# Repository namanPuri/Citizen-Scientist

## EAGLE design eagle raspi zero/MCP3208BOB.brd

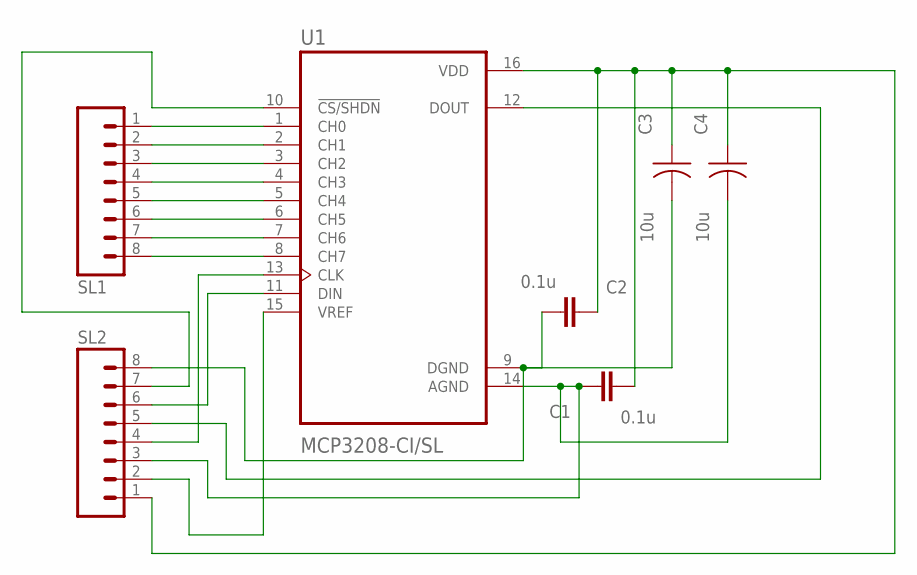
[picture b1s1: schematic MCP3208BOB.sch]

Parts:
C1, C2: 0.1u; CAP_0805
C3, C4: 10u; CAP_TANT_B
SL1, SL2: M08; 08P
U1: MCP3208-CI/SL; SOIC127P600X175-16N

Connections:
unnamed: C1.2, C2.1, C3.1, C4.1, SL2.1, U1.16 (VDD)
unnamed: SL2.6, U1.11 (DIN)
unnamed: C1.1, C4.2, SL2.3, U1.14 (AGND)
unnamed: SL1.1, U1.1 (CH0)
unnamed: SL1.2, U1.2 (CH1)
unnamed: SL1.3, U1.3 (CH2)
unnamed: SL1.4, U1.4 (CH3)
unnamed: SL1.5, U1.5 (CH4)
unnamed: SL1.7, U1.7 (CH6)
unnamed: SL1.6, U1.6 (CH5)
unnamed: SL1.8, U1.8 (CH7)
unnamed: C2.2, C3.2, SL2.8, U1.9 (DGND)
unnamed: SL2.5, U1.12 (DOUT)
unnamed: SL2.7, U1.10 (!CS/SHDN)
unnamed: SL2.4, U1.13 (CLK)
unnamed: SL2.2, U1.15 (VREF)

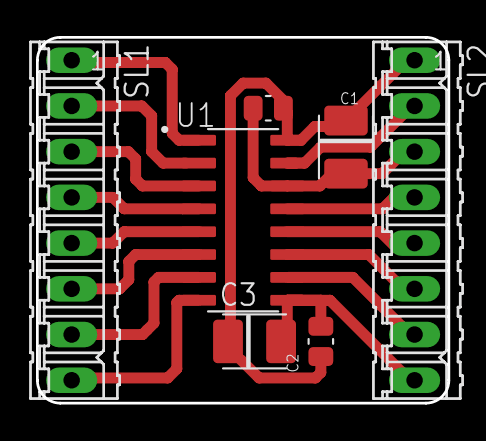
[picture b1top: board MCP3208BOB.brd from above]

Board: 2 copper layers, 22.9 x 20.3 mm, 7 parts (0 on the bottom side), 16 nets.

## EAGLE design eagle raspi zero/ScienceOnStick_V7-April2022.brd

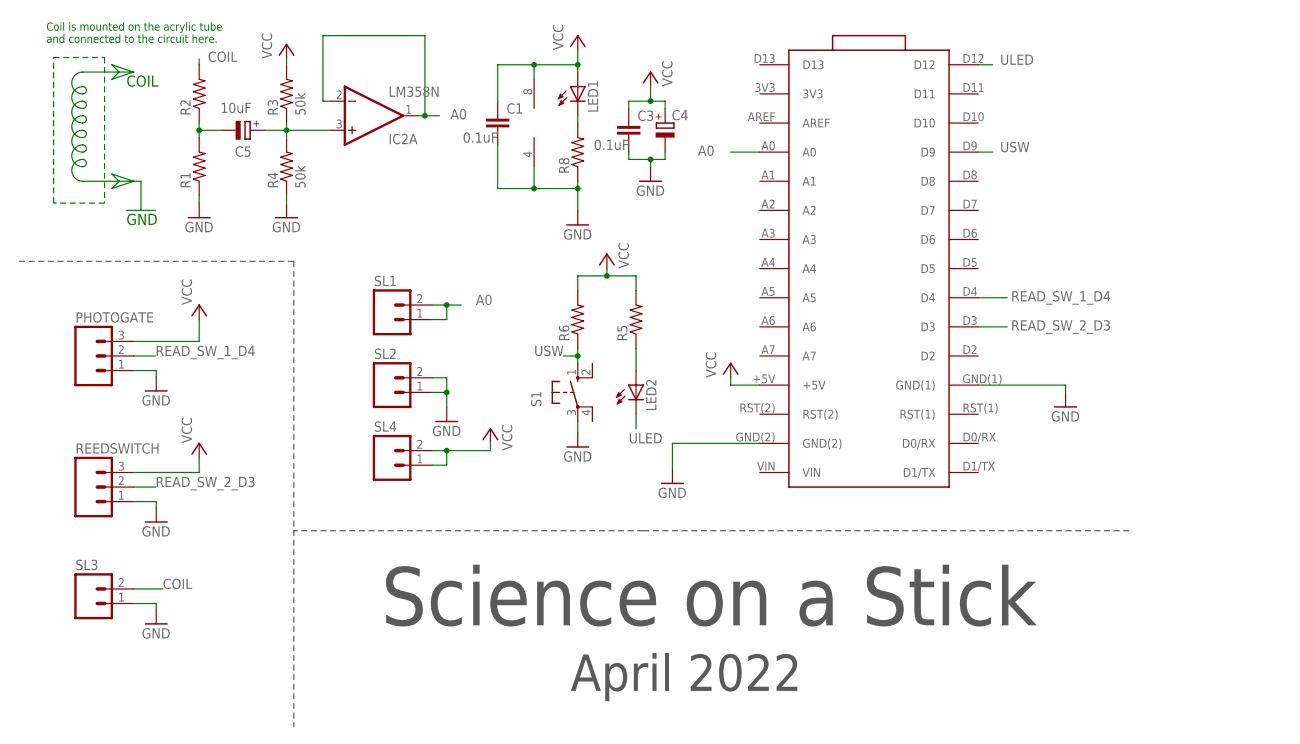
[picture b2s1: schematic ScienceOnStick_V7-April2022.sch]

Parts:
C1, C3: 0.1uF; C025-025X050
C4: CPOL-EUE2.5-6; E2,5-6
C5: 10uF; E2,5-6
IC2: LM358N; DIL08
LED1, LED2: LED3MM
PHOTOGATE: M03; 03P
R1, R2, R5, R6, R8: RESISTOR0207/7; 0207/7
R3, R4: 50k; 0207/7
REEDSWITCH: M03; 03P
S1: 40-XX; B3F-40XX
SL1, SL2, SL3, SL4: M02; 02P
U$1: ARDUINO_NANO_3_ARDUINO(NANO_3.0); ARDUINO_NANO_3_ARDUINO_NANO_30PIN

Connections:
A0: IC2.1 (OUT), IC2.2 (-IN), SL1.1, SL1.2, U$1.A0
CLAMP_SIGNAL: C5.+, IC2.3 (+IN), R3.1, R4.2
COIL: R2.2, SL3.2
GND: C1.2, C3.2, C4.-, IC2.4 (V-), PHOTOGATE.1, R1.1, R4.1, R8.1, REEDSWITCH.1, S1.3, SL2.1, SL2.2, SL3.1, U$1.GND(1), U$1.GND(2)
unnamed: C5.-, R1.2, R2.1
unnamed: LED2.A, R5.1
unnamed: LED1.K (C), R8.2
READ_SW_1_D4: PHOTOGATE.2, U$1.D4
READ_SW_2_D3: REEDSWITCH.2, U$1.D3
ULED: LED2.K (C), U$1.D12
USW: R6.1, S1.1 (S), U$1.D9
VCC: C1.1, C3.1, C4.+, IC2.8 (V+), LED1.A, PHOTOGATE.3, R3.2, R5.2, R6.2, REEDSWITCH.3, SL4.1, SL4.2, U$1.+5V

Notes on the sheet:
Science on a Stick
April 2022
Coil is mounted on the acrylic tube and connected to the circuit here.
COIL
GND

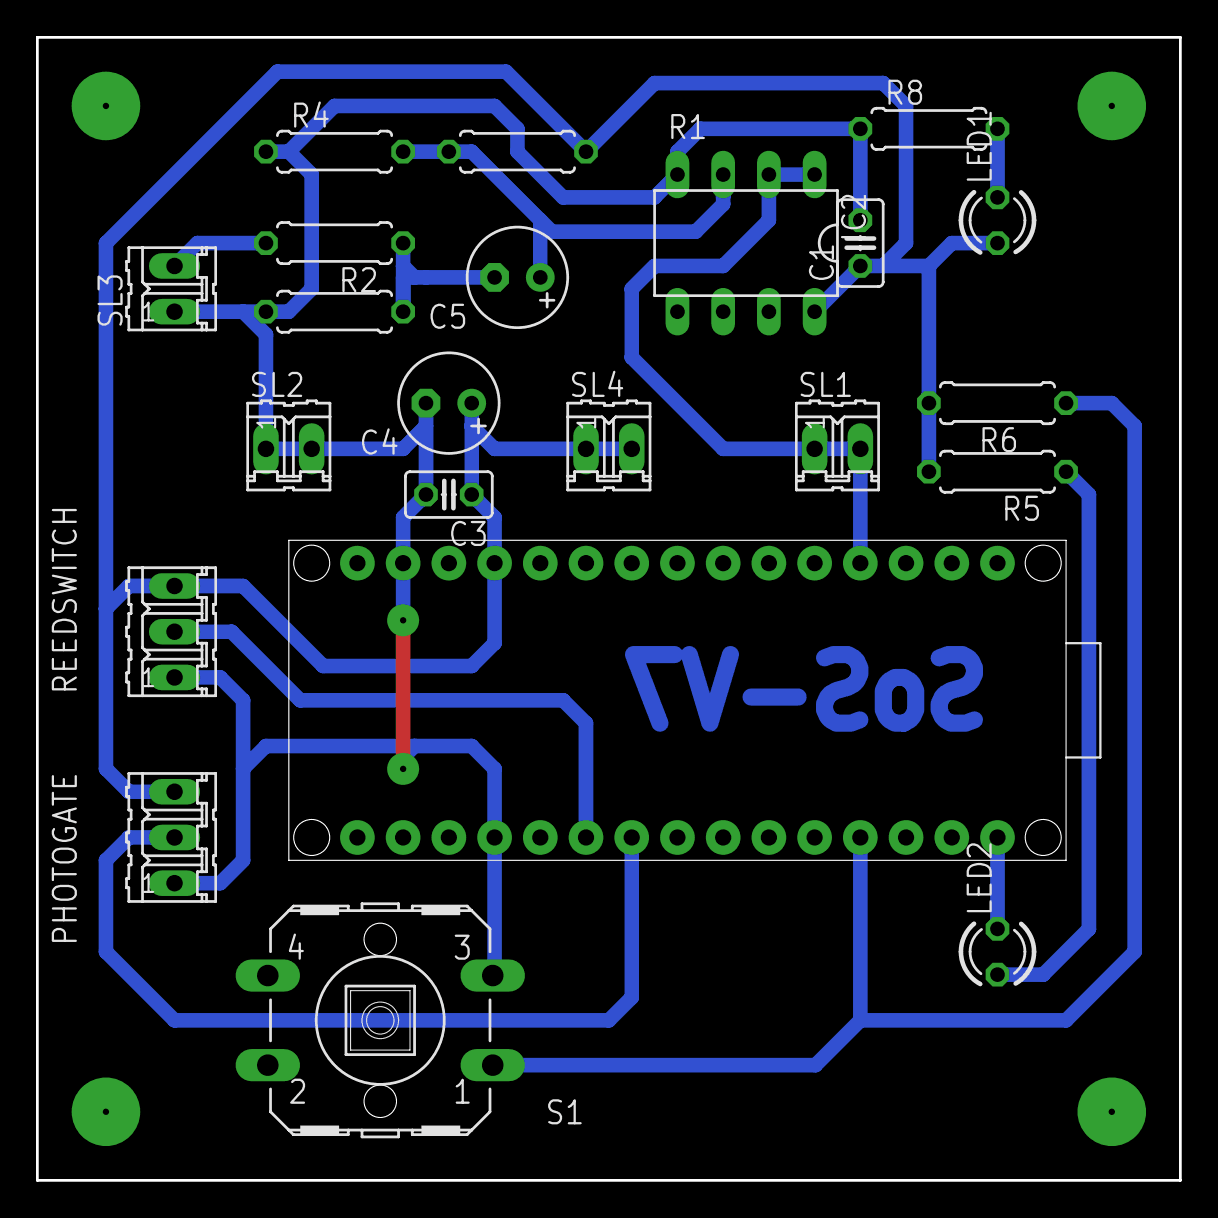
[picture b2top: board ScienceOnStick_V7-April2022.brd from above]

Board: 2 copper layers, 63.5 x 63.5 mm, 22 parts (0 on the bottom side), 12 nets.

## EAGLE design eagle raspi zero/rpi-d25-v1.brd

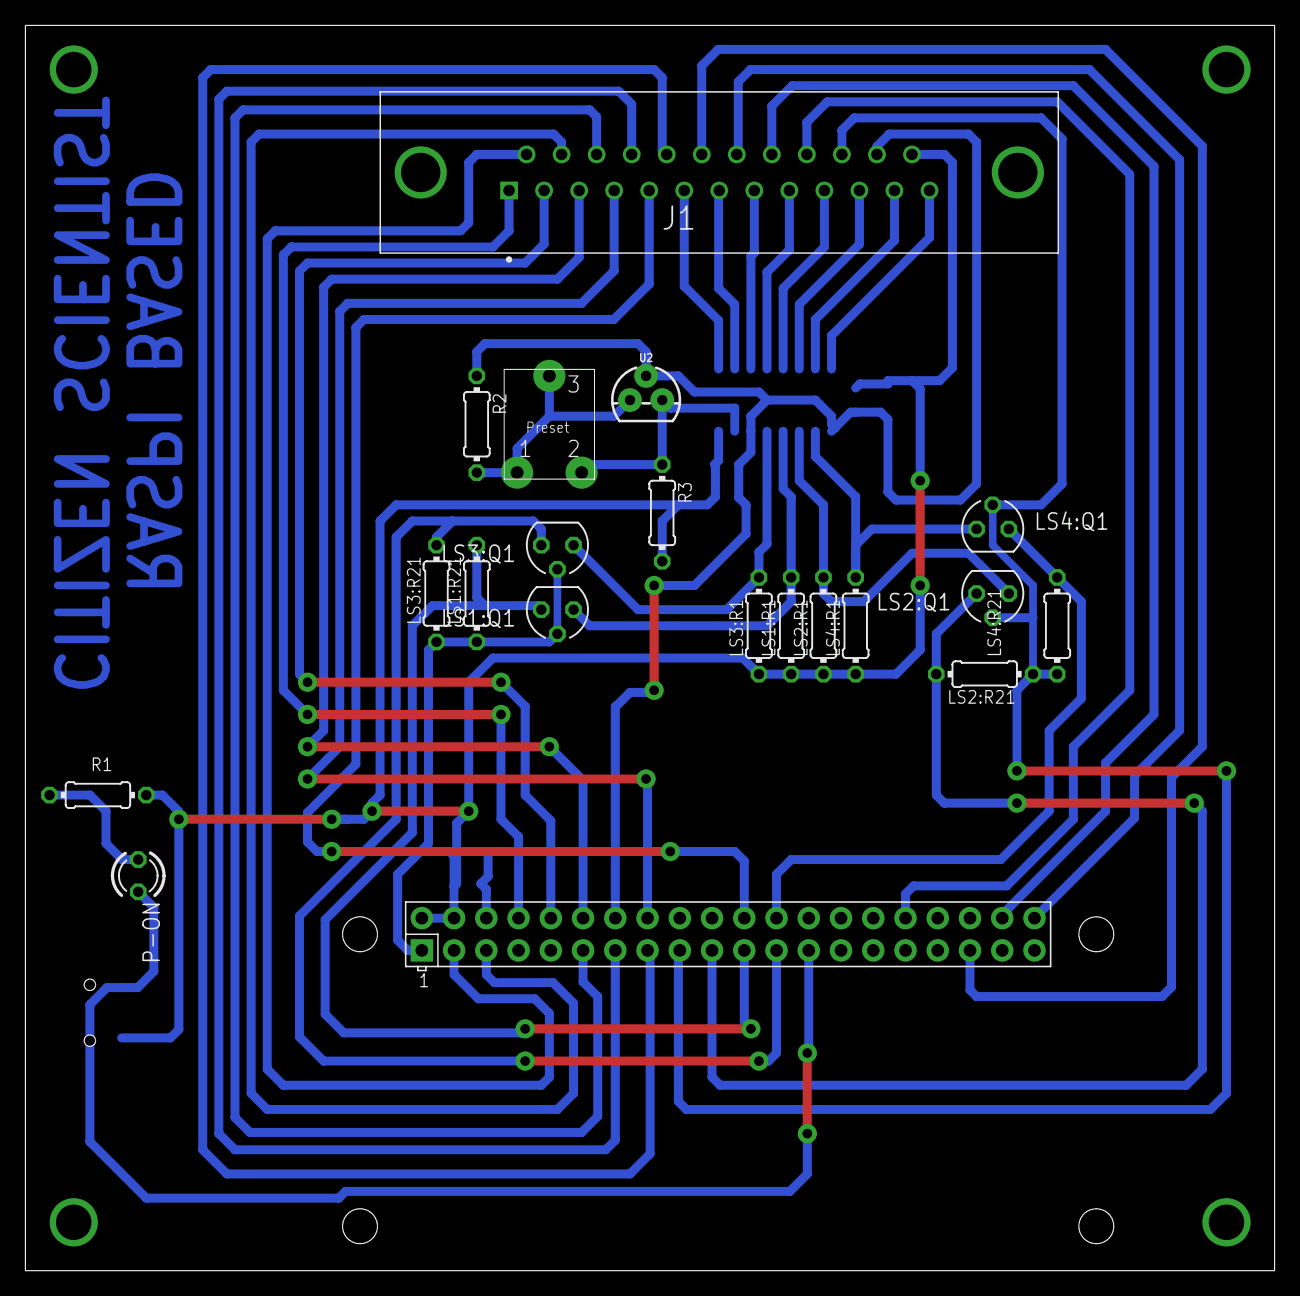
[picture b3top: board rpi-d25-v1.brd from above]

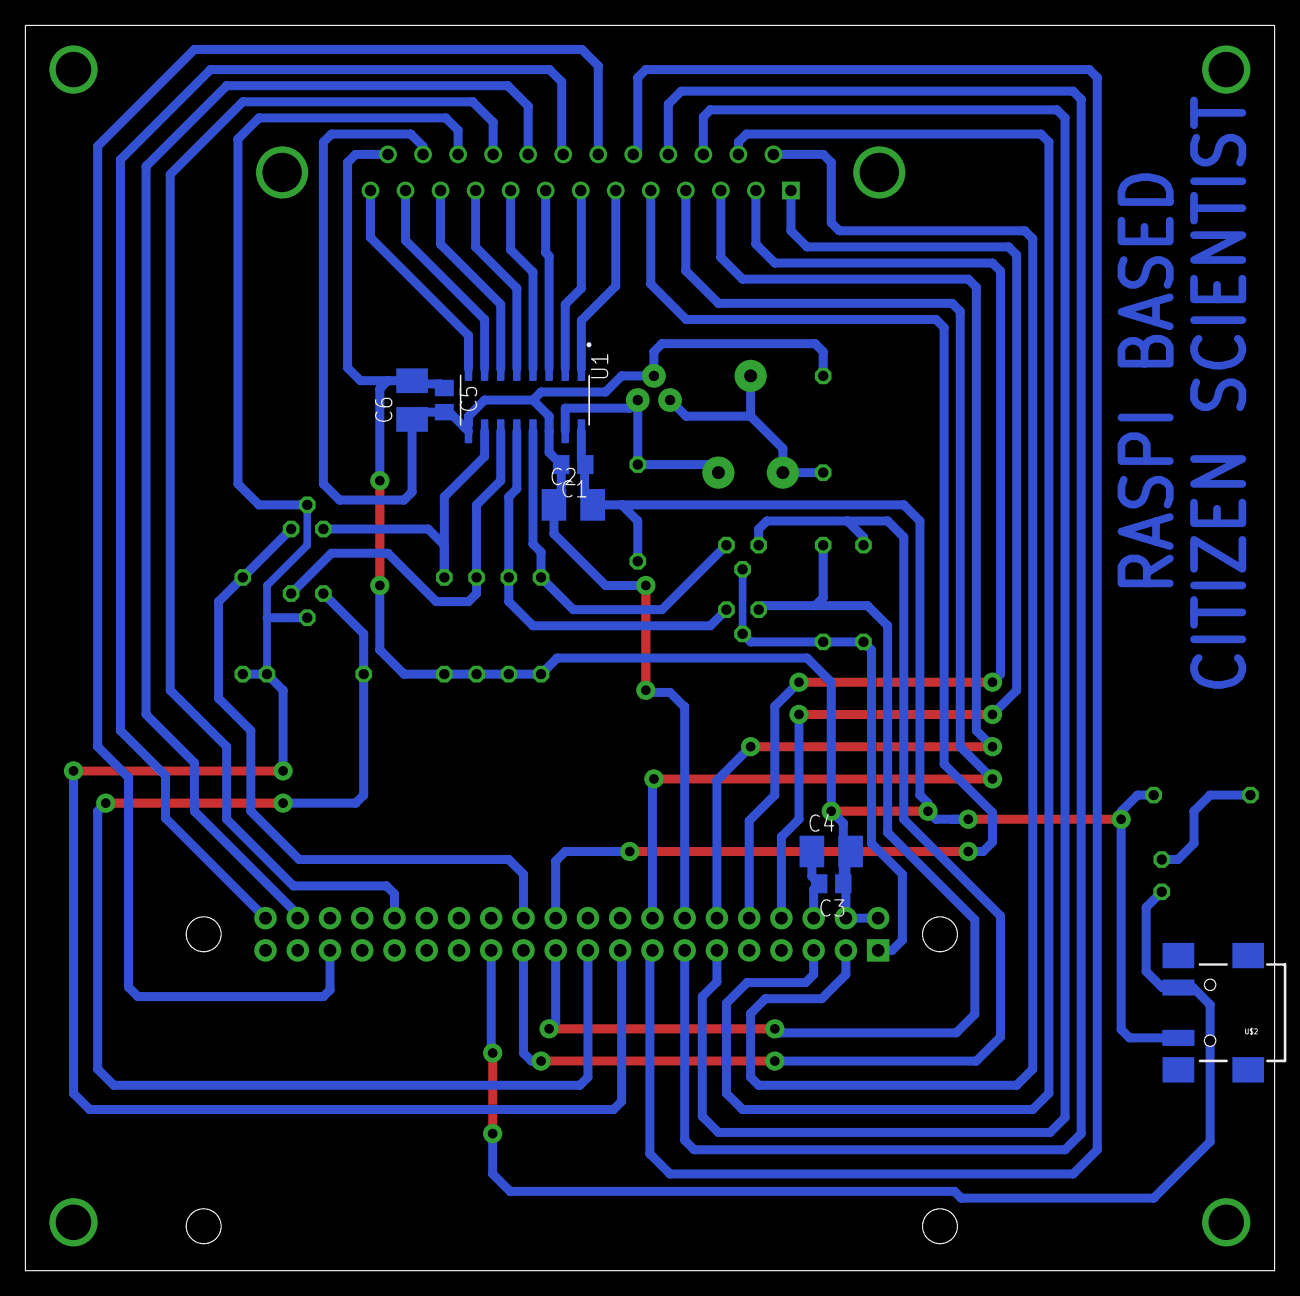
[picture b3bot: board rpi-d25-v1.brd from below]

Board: 2 copper layers, 98.4 x 98.1 mm, 28 parts (8 on the bottom side), 36 nets.

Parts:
C1, C3, C5: C0805
C2, C4, C6: B/3528-21R
J1: D25S24A4GV00LF
LS1:Q1, LS2:Q1, LS3:Q1, LS4:Q1: BS170; SOT54E
LS1:R1, LS1:R21, LS2:R1, LS2:R21, LS3:R1, LS3:R21, LS4:R1, LS4:R21: 10k; 0204/7
P-ON: LED3MM
PRESET1: 10k; PRESET_LR
R1: 4.7k; 0204/7
R2: 10k; 0204/7
R3: 150; 0204/7
U1: MCP3208-CI/SL; SOIC127P600X175-16N
U2: TL431PTH; TO-92
U$1: RPI-ZERO; RASP_PI_ZERO_BOARD_FULL
U$2: USB(POWER)

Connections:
+3V3: J1.23, LS1:Q1.G, LS1:R21.1, LS2:Q1.G, LS2:R21.1, LS3:Q1.G, LS3:R21.1, LS4:Q1.G, LS4:R21.1, U$1.1, U$1.17
+5V: C1.1, C2.+, C3.1, C4.+, C5.1, C6.+, J1.25, LS1:R1.1, LS2:R1.1, LS3:R1.1, LS4:R1.1, R1.2, R3.2, U1.16, U$1.2, U$1.4, U$2.VBUS
ADC-0: J1.6, U1.1
ADC-1: J1.7, U1.2
ADC-2: J1.8, U1.3
ADC-3: J1.9, U1.4
ADC-4: J1.10, U1.5
ADC-5: J1.11, U1.6
ADC-6: J1.12, U1.7
ADC-7: J1.13, U1.8
CLK-3: LS3:Q1.S, LS3:R21.2, U$1.23
CLK-5: LS3:Q1.D, LS3:R1.2, U1.13
CS-3: LS4:Q1.S, LS4:R21.2, U$1.24
CS-5: LS4:Q1.D, LS4:R1.2, U1.10
GND: C1.2, C2.-, C3.2, C4.-, C5.2, C6.-, J1.24, P-ON.K, R2.1, U1.9, U1.14, U2.2, U$1.6, U$1.9, U$1.14, U$1.20, U$1.25, U$1.30, U$1.34, U$1.39, U$2.GND
IO17: J1.16, U$1.11
IO22: J1.18, U$1.15
IO23: J1.4, U$1.16
IO25: J1.5, U$1.22
IO27: J1.17, U$1.13
MISO-3: LS1:Q1.S, LS1:R21.2, U$1.21
MISO-5: LS1:Q1.D, LS1:R1.2, U1.12
MOSI-3: LS2:Q1.S, LS2:R21.2, U$1.19
MOSI-5: LS2:Q1.D, LS2:R1.2, U1.11
unnamed: P-ON.A, R1.1
unnamed: PRESET1.P$1, PRESET1.P$3, R2.2, U2.1
unnamed: PRESET1.P$2, R3.1, U1.15, U2.3
PWM0: J1.22, U$1.32
SCL: J1.15, U$1.5
SDA: J1.14, U$1.3
SPI1-CLK: J1.20, U$1.40
SPI1-CS: J1.3, U$1.12
SPI1-MISO: J1.19, U$1.35
SPI1-MOSI: J1.21, U$1.38
UART-RX: J1.2, U$1.10
UART-TX: J1.1, U$1.8

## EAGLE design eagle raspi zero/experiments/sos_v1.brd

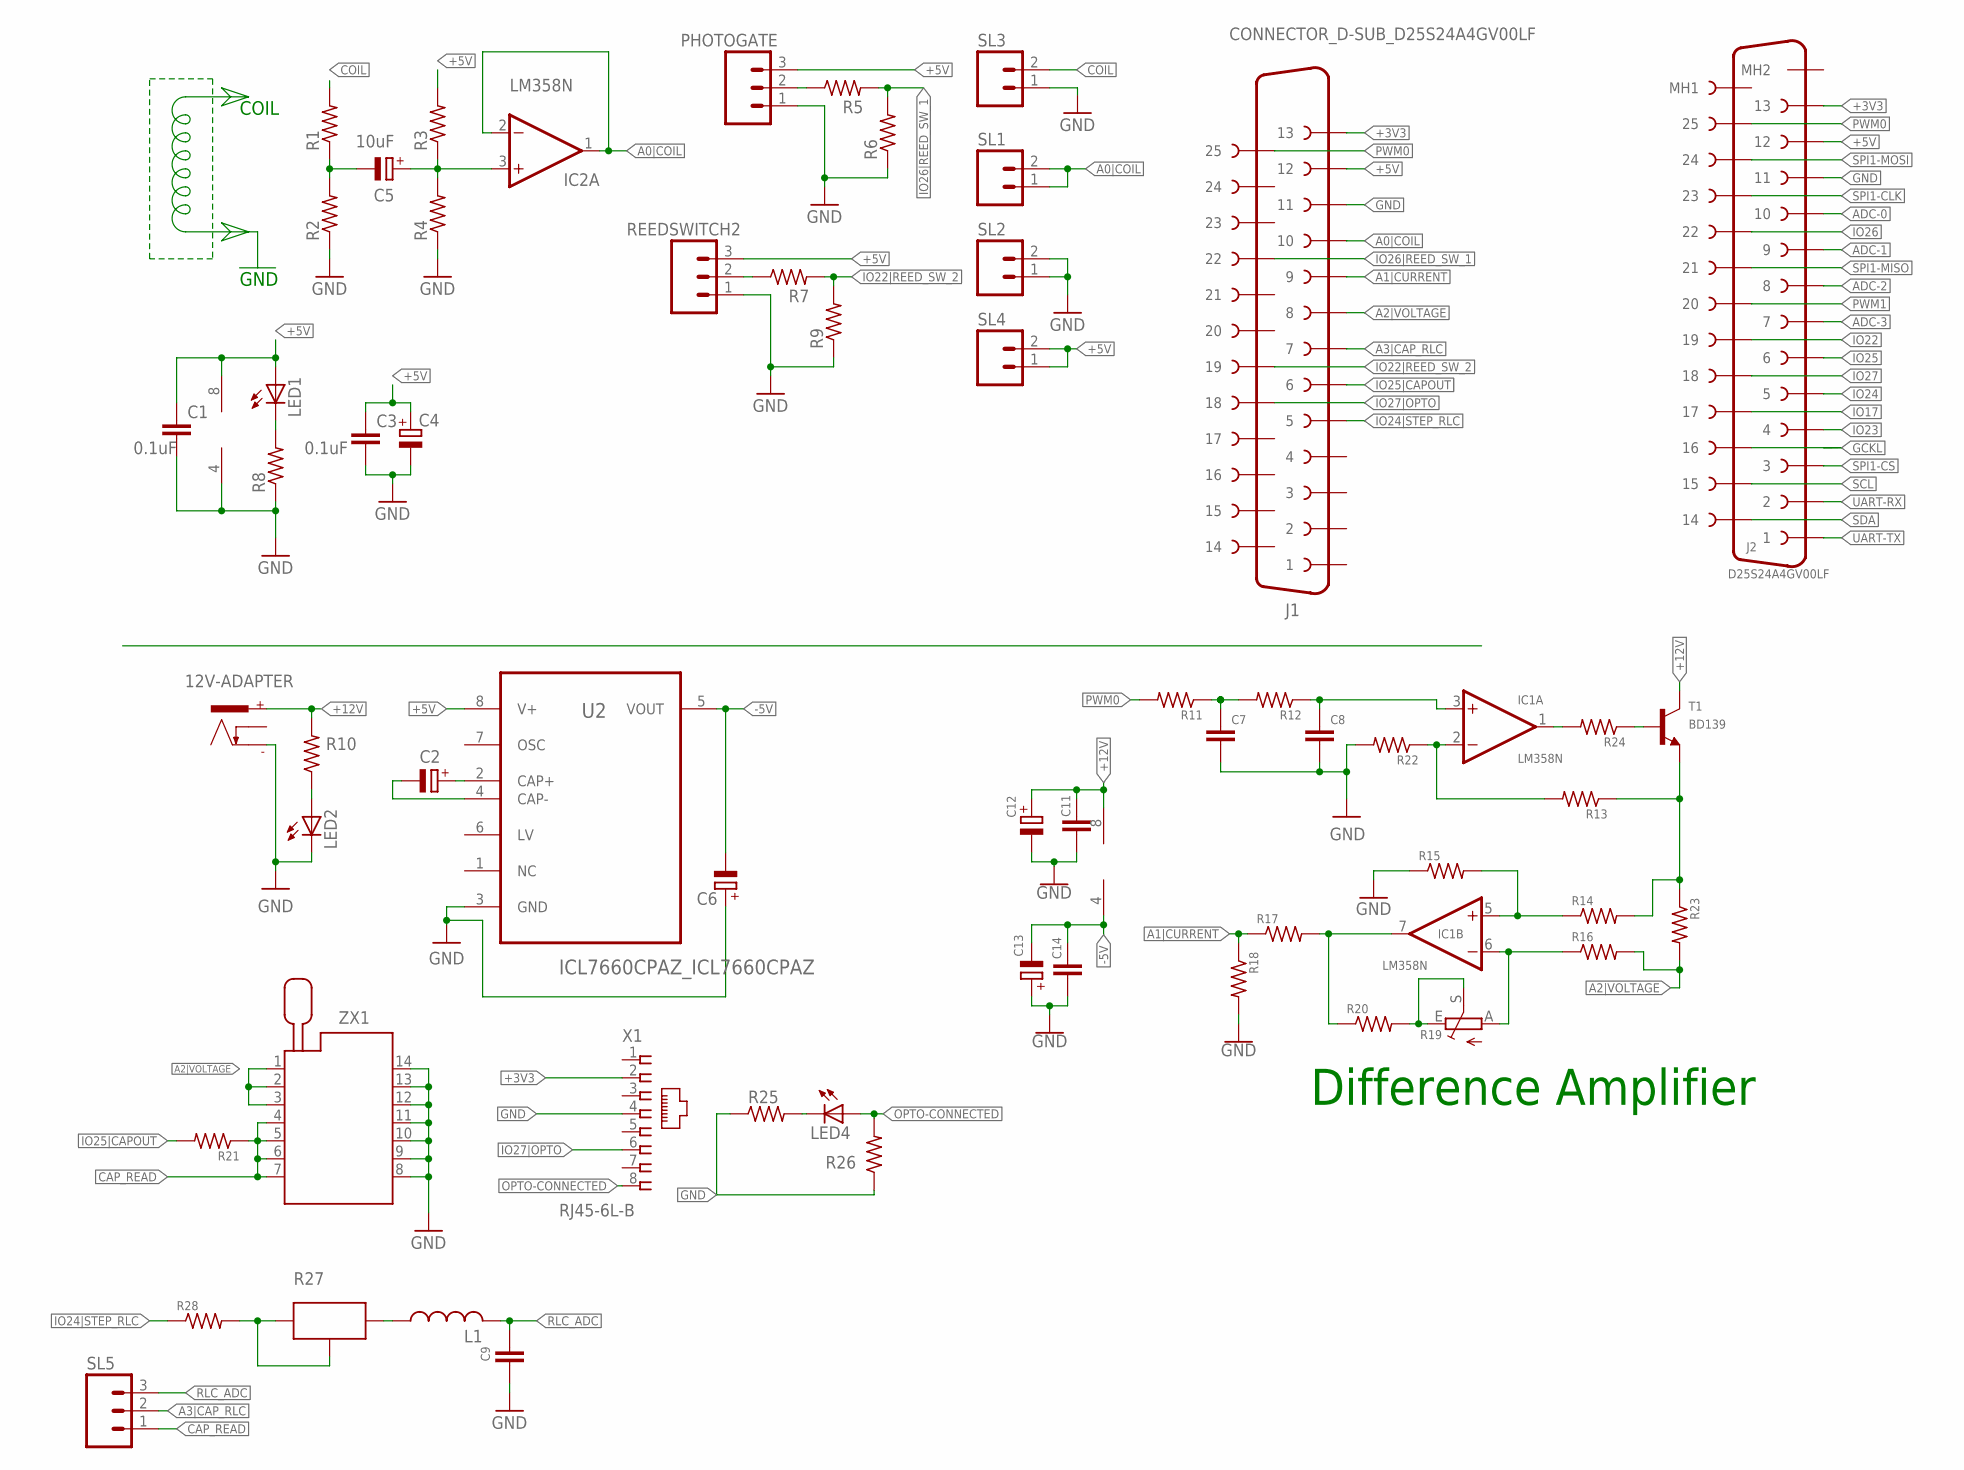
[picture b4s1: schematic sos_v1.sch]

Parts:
12V-ADAPTER: POWER_CON; NEB21R
C1, C3: 0.1uF; C025-025X050
C2, C6, C12, C13: CPOL-EUTT2D5; TT2D5
C4: CPOL-EUE2.5-6; E2,5-6
C5: 10uF; E2,5-6
C7, C8, C9, C11, C14: C-EU025-025X050; C025-025X050
IC1, IC2: LM358N; DIL08
J1: CONNECTOR_D-SUB_D25S24A4GV00LF
J2: D25S24A4GV00LF
L1: L-USTJ3-U2; TJ3-U2
LED1, LED2, LED4: LED3MM
PHOTOGATE: M03; 03P
R1, R2, R3, R4, R5, R6, R7, R8, R9, R10, R11, R12, R13, R14, R15, R16, R17, R18, R20, R21, R22, R24, R25, R26: R-US_0204/7; 0204/7
R19: TRIM_EU-RJ9W; RJ9W
R23, R28: R-US_0207/10; 0207/10
R27: POTNORMAL; RJ9W
REEDSWITCH2: M03; 03P
SL1, SL2, SL3, SL4: M02; 02P
SL5: M03; 03P
T1: BD139; TO126
U2: ICL7660CPAZ_ICL7660CPAZ; ICL7660CPAZ_DIP254P762X533-8
X1: RJ45-6L-B; RJ45-NO-SHIELD
ZX1: 214-3339-00-0602J

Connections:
+3V3: J1.P$13 (13), J2.13, X1.2
+5V: C1.1, C3.1, C4.+, IC2.8 (V+), J1.P$14 (12), J2.12, LED1.A, PHOTOGATE.3, R3.2, REEDSWITCH2.3, SL4.1, SL4.2, U2.8 (V+)
+12V: 12V-ADAPTER.+, C11.1, C12.+, IC1.8 (V+), R10.2, T1.2 (C)
-5V: C6.-, C13.-, C14.1, IC1.4 (V-), U2.5 (VOUT)
A0|COIL: IC2.1 (OUT), IC2.2 (-IN), J1.P$16 (10), SL1.1, SL1.2
A1|CURRENT: J1.P$17 (9), R17.1, R18.1
A2|VOLTAGE: J1.P$18 (8), R16.2, R23.2, ZX1.1, ZX1.2, ZX1.3
A3|CAP_RLC: J1.P$19 (7), SL5.2
ADC-0: J2.10
ADC-1: J2.9
ADC-2: J2.8
ADC-3: J2.7
CAP_READ: R21.1, SL5.1, ZX1.4, ZX1.5, ZX1.6, ZX1.7
CLAMP_SIGNAL: C5.+, IC2.3 (+IN), R3.1, R4.2
COIL: R1.2, SL3.2
GCKL: J2.16
GND: 12V-ADAPTER.-, C1.2, C3.2, C4.-, C6.+, C7.2, C8.2, C9.2, C11.2, C12.-, C13.+, C14.2, IC2.4 (V-), J1.P$15 (11), J2.11, LED2.K (C), PHOTOGATE.1, R2.1, R4.1, R6.1, R8.1, R9.1, R15.1, R18.2, R22.2, R25.1, R26.1, REEDSWITCH2.1, SL2.1, SL2.2, SL3.1, U2.3 (GND), X1.4, ZX1.8, ZX1.9, ZX1.10, ZX1.11, ZX1.12, ZX1.13, ZX1.14
IO17: J2.17
IO22: J2.19
IO22|REED_SW_2: J1.P$7 (19), R7.2, R9.2
IO23: J2.4
IO24: J2.5
IO24|STEP_RLC: J1.P$21 (5), R28.1
IO25: J2.6
IO25|CAPOUT: J1.P$20 (6), R21.2
IO26: J2.22
IO26|REED_SW_1: J1.P$4 (22), R5.2, R6.2
IO27: J2.18
IO27|OPTO: J1.P$8 (18), X1.6
unnamed: C5.-, R1.1, R2.2
unnamed: PHOTOGATE.2, R5.1
unnamed: R7.1, REEDSWITCH2.2
unnamed: LED1.K (C), R8.2
unnamed: C2.+, U2.2 (CAP+)
unnamed: C2.-, U2.4 (CAP-)
unnamed: C7.1, R11.1, R12.2
unnamed: LED2.A, R10.1
unnamed: IC1.1 (OUT), R24.2
unnamed: R24.1, T1.3 (B)
unnamed: C8.1, IC1.3 (+IN), R12.1
unnamed: IC1.2 (-IN), R13.2, R22.1
unnamed: IC1.5 (+IN), R14.1, R15.2
unnamed: IC1.6 (-IN), R16.1, R19.A
unnamed: R13.1, R14.2, R23.1, T1.1 (E)
unnamed: R19.E, R19.S, R20.2
unnamed: IC1.7 (OUT), R17.2, R20.1
unnamed: LED4.K (C), R25.2
unnamed: R27.E, R27.S, R28.2
unnamed: L1.1, R27.A
OPTO-CONNECTED: LED4.A, R26.2, X1.8
PWM0: J1.P$1 (25), J2.25, R11.2
PWM1: J2.20
RLC_ADC: C9.1, L1.2, SL5.3
SCL: J2.15
SDA: J2.14
SPI1-CLK: J2.23
SPI1-CS: J2.3
SPI1-MISO: J2.21
SPI1-MOSI: J2.24
UART-RX: J2.2
UART-TX: J2.1

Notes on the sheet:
COIL
GND
Difference Amplifier

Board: 2 copper layers, 61 parts (0 on the bottom side), 40 nets, no tracks yet.

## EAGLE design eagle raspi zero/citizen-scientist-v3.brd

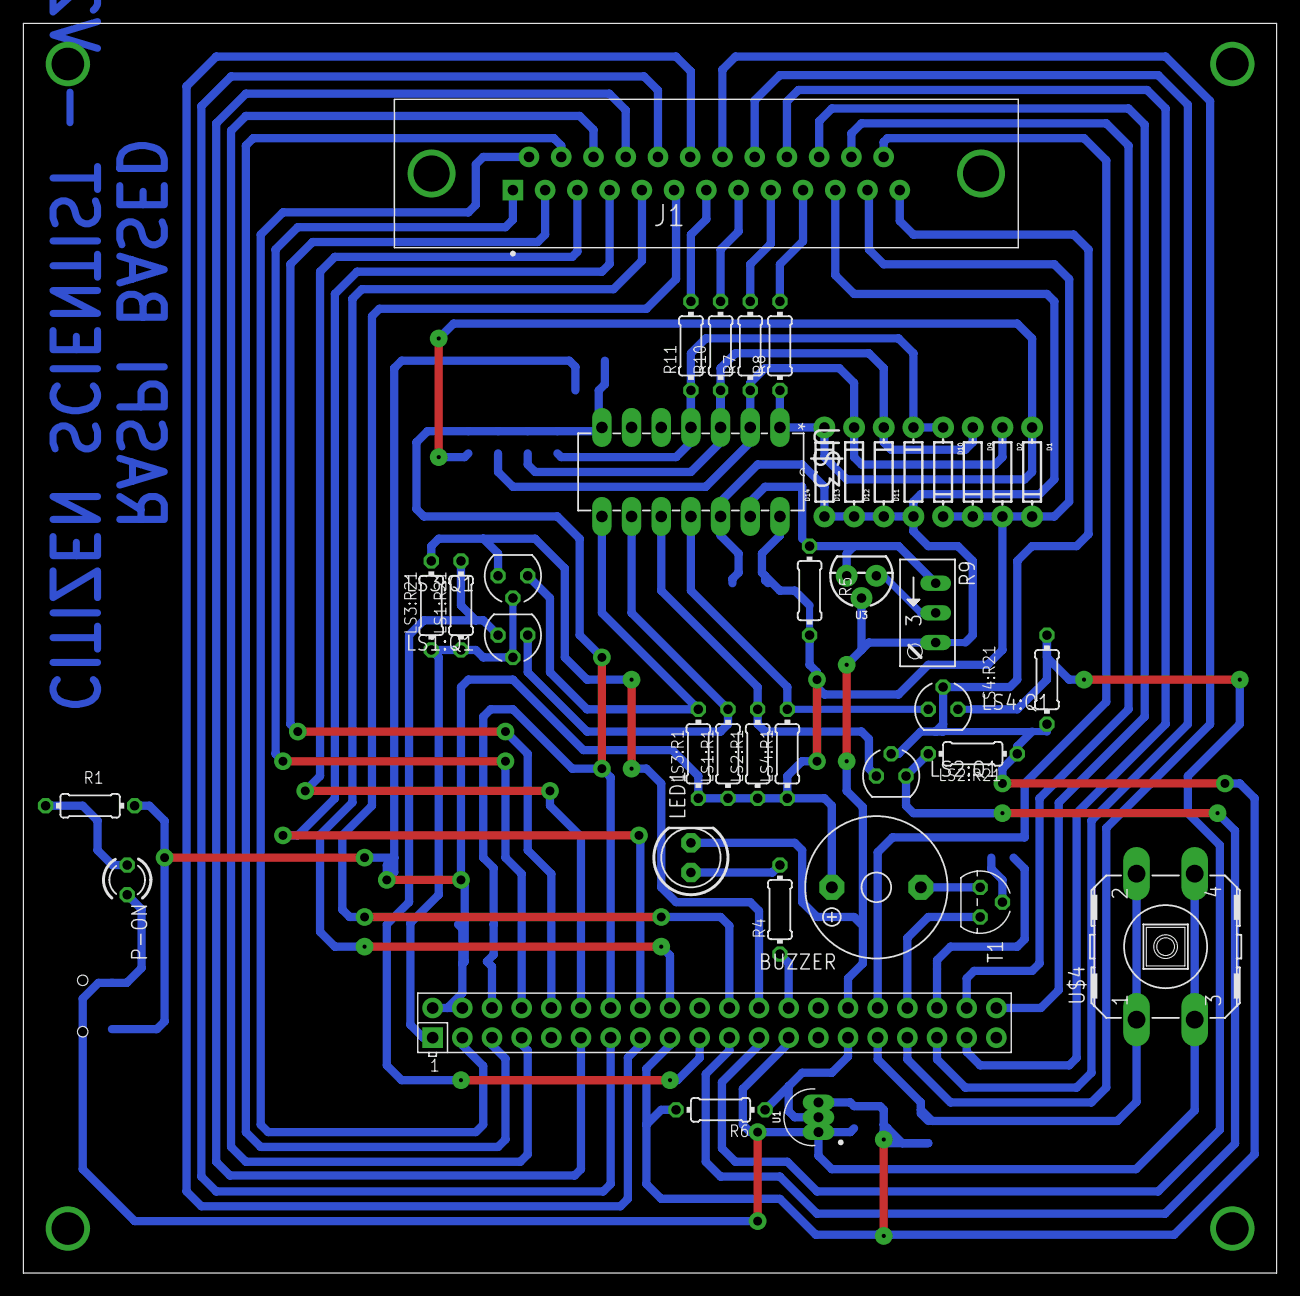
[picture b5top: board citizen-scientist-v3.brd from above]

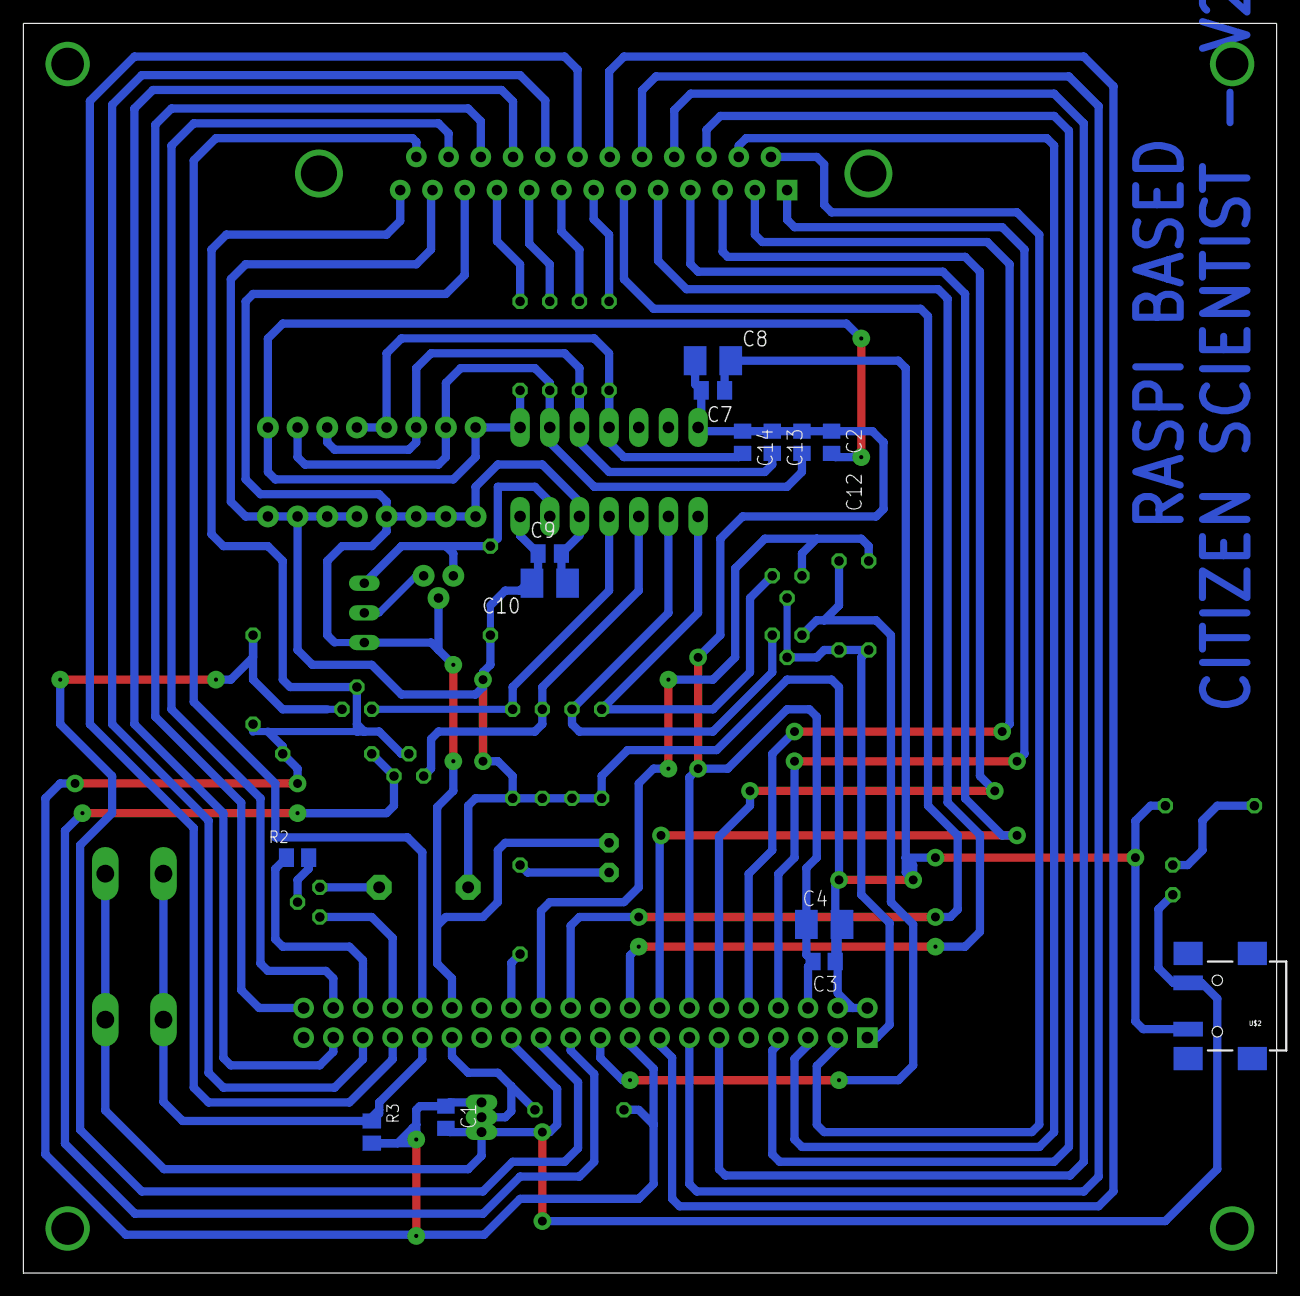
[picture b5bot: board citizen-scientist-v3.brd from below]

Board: 2 copper layers, 107.3 x 107.0 mm, 53 parts (14 on the bottom side), 47 nets.

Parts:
BUZZER: BUZZER; F/TMB
C1, C3: 0.1u; C0805
C2, C12, C13, C14: 1n; C0805
C4, C8, C10: 10u; B/3528-21R
C7, C9: 0.1u; C0805K
D1, D2, D9, D10, D11, D12, D13, D14: DIODE-1N4148
J1: D25S24A4GV00LF
LED1: LED5MM
LS1:Q1, LS2:Q1, LS3:Q1, LS4:Q1: BS170; SOT54E
LS1:R1, LS1:R21, LS2:R1, LS2:R21, LS3:R1, LS3:R21, LS4:R1, LS4:R21: 10k; 0204/7
P-ON: LED3MM
R1, R6: 4.7k; 0204/7
R2: 1k; M0805
R3: 10k; M0805
R4: 2.2k; 0204/7
R5: 150; 0204/7
R7, R8, R10, R11: 3.3k; 0204/7
R9: 10k; RJ9W
T1: BC547; TO92
U1: DS18B20; TO-92-TO92127P495H2044-3
U3: TL431PTH; TO-92
U$1: RPI-ZERO; RASP_PI_ZERO_BOARD_FULL
U$2: USB(POWER)
U$3: MCP3204-CI/P; DIP254P762X432-14
U$4: OMRON_SWITCH_40-XX; B3F-40XX

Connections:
+3V3: C1.1, J1.13, LS1:Q1.G, LS1:R21.1, LS2:Q1.G, LS2:R21.1, LS3:Q1.G, LS3:R21.1, LS4:Q1.G, LS4:R21.1, R3.2, R6.2, U1.3, U$1.1, U$1.17
+5V: BUZZER.+, C3.1, C4.+, C7.1, C8.+, C9.1, C10.+, D1.C, D2.C, D9.C, D10.C, J1.12, LS1:R1.1, LS2:R1.1, LS3:R1.1, LS4:R1.1, R1.2, R5.2, U$1.2, U$1.4, U$2.VBUS, U$3.14
ADC-0: J1.10, R8.2
ADC-1: J1.9, R7.2
ADC-2: J1.8, R10.2
ADC-3: J1.7, R11.2
BUTTON: R3.1, U$1.31, U$4.1, U$4.2
BUZZER: R2.1, U$1.36
CLK-3: LS4:Q1.S, LS4:R21.2, U$1.23
CLK-5: LS4:Q1.D, LS4:R1.2, U$3.11
CS-3: LS3:Q1.S, LS3:R21.2, U$1.24
CS-5: LS3:Q1.D, LS3:R1.2, U$3.8
GCKL: J1.16, U$1.7
GND: C1.2, C2.1, C3.2, C4.-, C7.2, C8.-, C9.2, C10.-, C12.1, C13.1, C14.1, D11.A, D12.A, D13.A, D14.A, J1.11, LED1.K, P-ON.K, R9.A, T1.1, U1.1, U3.2, U$1.6, U$1.9, U$1.14, U$1.20, U$1.25, U$1.30, U$1.34, U$1.39, U$2.GND, U$3.7, U$3.12, U$4.3, U$4.4
IO17: J1.17, U$1.11
IO22: J1.19, U$1.15
IO23: J1.4, U$1.16
IO24: J1.5, U$1.18
IO25: J1.6, U$1.22
IO26: J1.22, U$1.37
IO27: J1.18, U$1.13
LED: R4.1, U$1.26
MISO-3: LS2:Q1.S, LS2:R21.2, U$1.21
MISO-5: LS2:Q1.D, LS2:R1.2, U$3.10
MOSI-3: LS1:Q1.S, LS1:R21.2, U$1.19
MOSI-5: LS1:Q1.D, LS1:R1.2, U$3.9
unnamed: P-ON.A, R1.1
unnamed: R9.S, U3.1
unnamed: R5.1, R9.E, U3.3, U$3.13
unnamed: R2.2, T1.2
unnamed: BUZZER.-, T1.3
unnamed: C2.2, D1.A, D14.C, R8.1, U$3.1
unnamed: LED1.A, R4.2
unnamed: C12.2, D2.A, D13.C, R7.1, U$3.2
unnamed: C13.2, D9.A, D12.C, R10.1, U$3.3
unnamed: C14.2, D10.A, D11.C, R11.1, U$3.4
PWM0: J1.25, U$1.32
PWM1: J1.20, U$1.33
SCL: J1.15, U$1.5
SDA: J1.14, U$1.3
SPI1-CLK: J1.23, U$1.40
SPI1-CS: J1.3, U$1.12
SPI1-MISO: J1.21, U$1.35
SPI1-MOSI: J1.24, U$1.38
TEMP: R6.1, U1.2, U$1.29
UART-RX: J1.2, U$1.10
UART-TX: J1.1, U$1.8

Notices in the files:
parts and their libraries:
SparkFun-DiscreteSemi: Licensing: Creative Commons ShareAlike 4.0 International - https://creativecommons.org/licenses/by-sa/4.0
